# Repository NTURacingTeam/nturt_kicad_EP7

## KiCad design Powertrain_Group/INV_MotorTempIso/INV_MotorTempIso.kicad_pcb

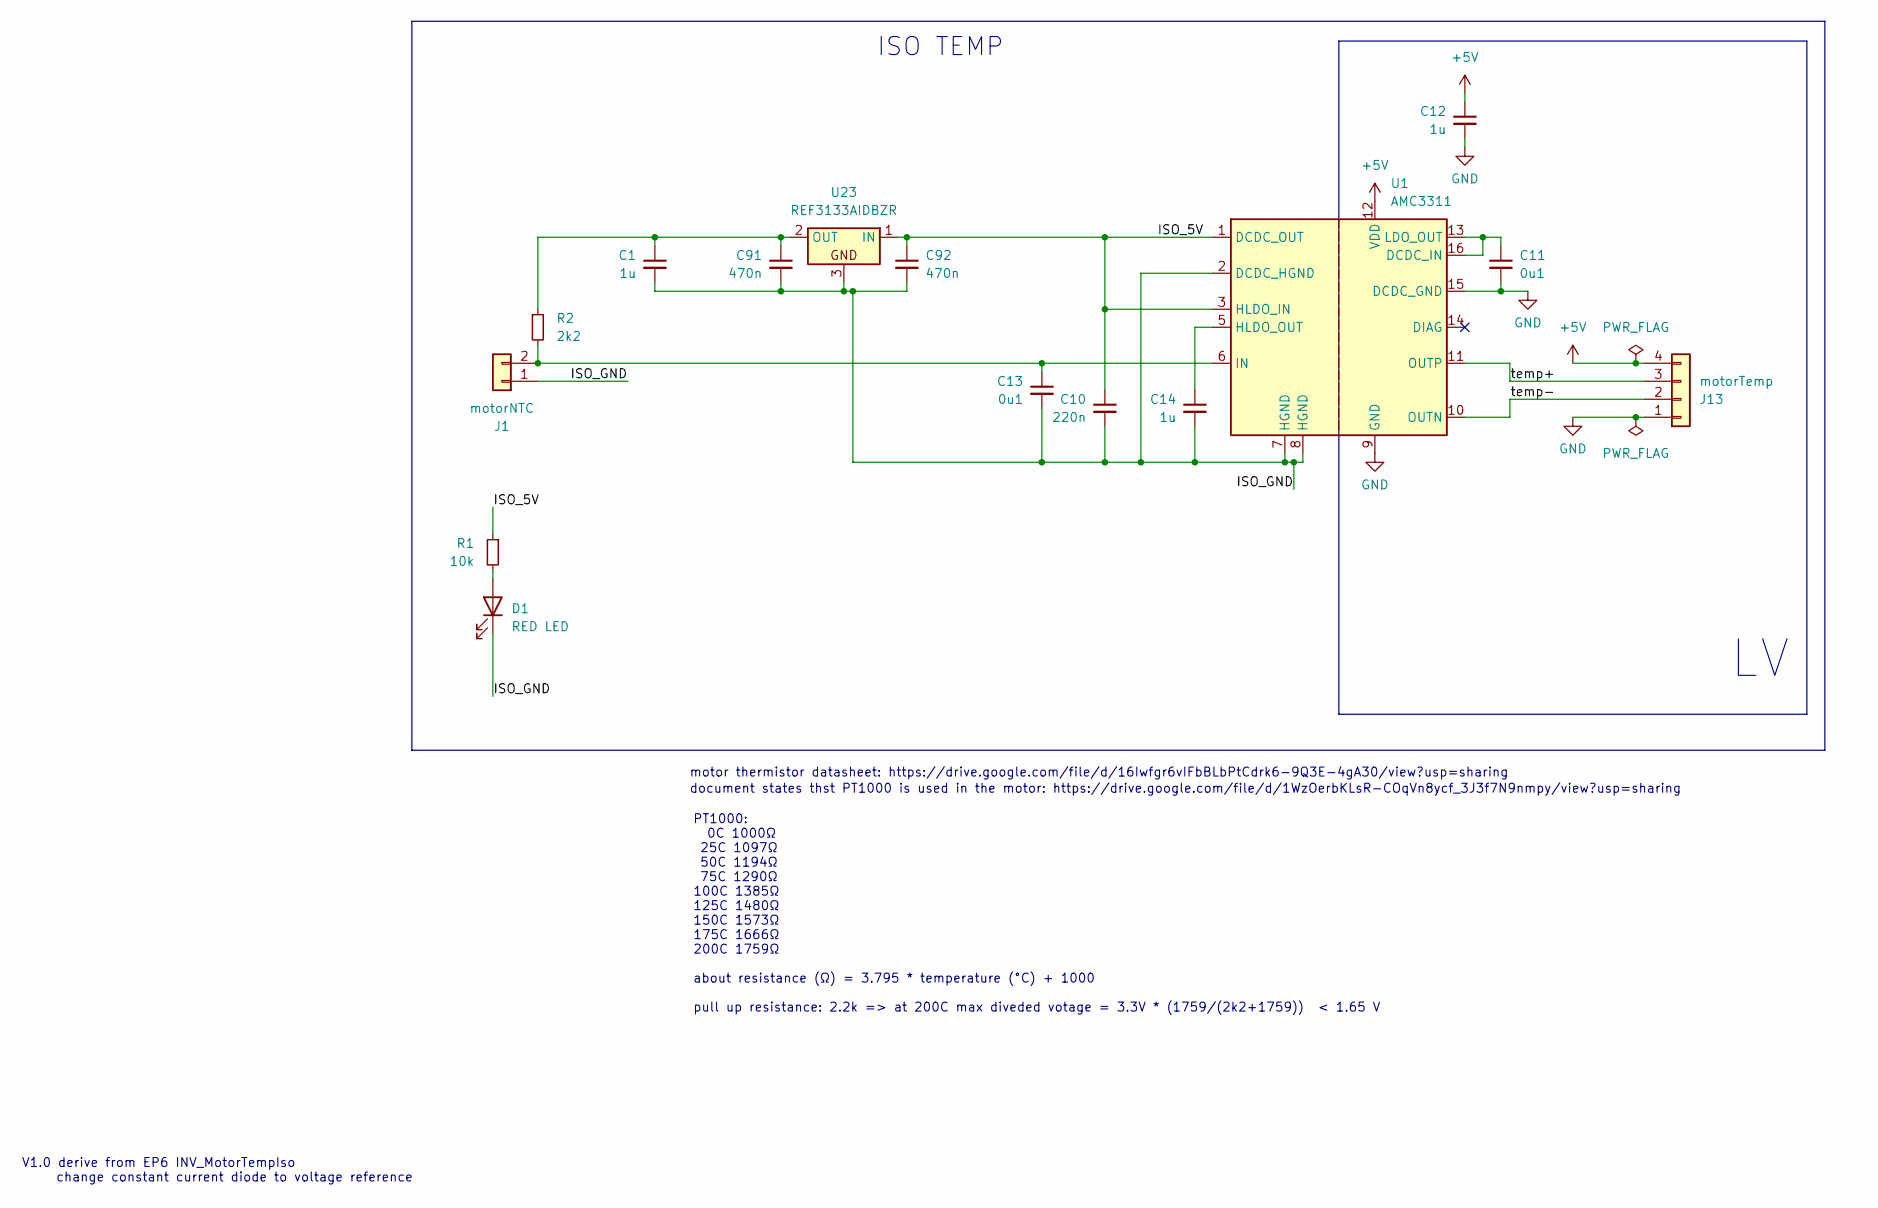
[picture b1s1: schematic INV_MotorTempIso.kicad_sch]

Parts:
C1, C12, C14: 1u; C_0603_1608Metric
C10: 220n; C_0603_1608Metric
C11, C13: 0u1; C_0603_1608Metric
C91, C92: 470n; C_0603_1608Metric
D1: RED LED; LED_0603_1608Metric
J1: motorNTC; JST_PH_S2B-PH-K_1x02_P2.00mm_Horizontal
J13: motorTemp; JST_PH_S4B-PH-K_1x04_P2.00mm_Horizontal
R1: 10k; R_0603_1608Metric
R2: 2k2; R_0603_1608Metric
U1: AMC3311; SOIC-16W_7.5x10.3mm_P1.27mm
U23: REF3133AIDBZR; SOT-23

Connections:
+5V: C12.1, J13.4, U1.12 (VDD)
/ISO_5V: C10.1, C92.1, R1.1, U1.1 (DCDC_OUT), U1.3 (HLDO_IN), U23.1 (IN)
/ISO_GND: C1.2, C10.2, C13.2, C14.2, C91.2, C92.2, D1.1 (K), J1.1, U1.2 (DCDC_HGND), U1.7 (HGND), U1.8 (HGND), U23.3
/temp+: J13.3, U1.11 (OUTP)
/temp-: J13.2, U1.10 (OUTN)
GND: C11.2, C12.2, J13.1, U1.9 (GND), U1.15 (DCDC_GND)
unnamed: D1.2 (A), R1.2
unnamed: C13.1, J1.2, R2.2, U1.6 (IN)
unnamed: C11.1, U1.13 (LDO_OUT), U1.16 (DCDC_IN)
unnamed: C14.1, U1.5 (HLDO_OUT)
unnamed: C1.1, C91.1, R2.1, U23.2 (OUT)

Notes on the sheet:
V1.0 derive from EP6 INV_MotorTempIso change constant current diode to voltage reference
document states thst PT1000 is used in the motor: https://drive.google.com/file/d/1WzOerbKLsR-COqVn8ycf_3J3f7N9nmpy/view?usp=sharing
motor thermistor datasheet: https://drive.google.com/file/d/16Iwfgr6vIFbBLbPtCdrk6-9Q3E-4gA30/view?usp=sharing
PT1000: 0C 1000Ω 25C 1097Ω 50C 1194Ω 75C 1290Ω 100C 1385Ω 125C 1480Ω 150C 1573Ω 175C 1666Ω 200C 1759Ω about resistance (Ω) = 3.795 * temperature (°C) + 1000 pull up resistance: 2.2k => at 200C max diveded votage = 3.3V * (1759/(2k2+1759)) < 1.65 V
ISO TEMP

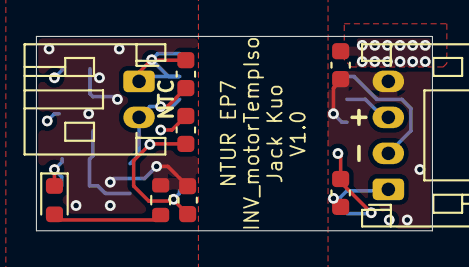
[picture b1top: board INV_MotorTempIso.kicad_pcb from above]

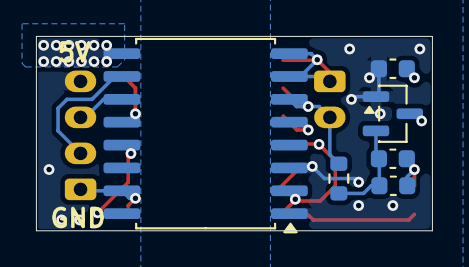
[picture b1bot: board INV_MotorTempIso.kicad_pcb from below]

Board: 4 copper layers, 22.0 x 10.8 mm, 15 parts (6 on the bottom side), 11 nets.
